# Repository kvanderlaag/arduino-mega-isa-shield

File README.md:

# Arduino Mega 2560 ISA Card Shield
 
 Diagnostic/Development shield for IBM PC XT/AT ISA cards.

 ## God, now what?
 
 Okay, listen. Sometimes you're developing an ISA card, and you fuck it up. Sometimes you want to be able to give that card a set of known inputs for a bus state, and probe around on the card to see why it's not doing what you expect. If we're being honest, that's usually pretty hard when the card is installed in a machine! Arduinos are easy as hell to write simple firmware for, so this is a shield (in an extremely non-standard form factor, you won't be stacking anything on top of this) that breaks most of the useful ISA signals out to an ISA card slot. Pin assignment is set up so that things generally live on sequential port pins wherever possible, and all of the weird ports that you don't get all of the pins for are set up so that they're grouped by whether they're expected to be driven by the bus master, or the card. (i.e. whether you're going to be reading or writing them from the Arduino.) This _should_ allow for reasonably fast access to setting/reading bus state.
 
 ## Does it suck?

Yes, the Arduino Mega 2560 is an 8MHz 8-bit AVR, it's going to be too slow to keep up with 14.31818 MHz ISA signalling in the strictest sense. This isn't going to be useful as a bus emulator, but for basic poking at cards and testing logic, it will work for a lot of cases.

## What sort of features does it have?

It breaks out the full 16-bit data bus, the full address bus for a 16-bit card, and all of the control signals you should need for both 8 and 16-bit reads and writes. Due to the number of available I/O pins on the arduino, it does only provide a small number of DMA channels and interrupts. Specifically, IRQ 2/9, 3, 5, and 7, and DMA channels 1, 3, 5, and 7. I'm using this mostly to test sound cards, for which these are all reasonable options -- it would probably be a good idea to add a jumper block to switch at least one of these out between the remaining options.

The Renesas clock generator/multiplier on the board produces a 14.31818MHz clock signal on the bus clock pin. If your card is using this pin to clock another part (like a Yamaha FM chip, or an SAA1099 sound generator, for instance), this will supply the correct frequency, but the Arduino won't be able to keep up with it. I'm interested to know how well this works for a variety of applications, so if you use this for anything, let me know!

## What AVR ports map to which ISA signals?

Pins not listed in a port are reserved for system use on the Arduino, so maybe don't read from or write to them.

### Port A

| AVR Pin | ISA Signal |
| --- | --- |
| PA0 | D0 |
| PA1 | D1 |
| PA2 | D2 |
| PA3 | D3 |
| PA4 | D4 |
| PA5 | D5 |
| PA6 | D6 |
| PA7 | D7 |

### Port B

| AVR Pin | ISA Signal |
| --- | --- |
| PB0 | A0 |
| PB1 | A1 |
| PB2 | A2 |
| PB3 | A3 |
| PB4 | A4 |
| PB5 | A5 |
| PB6 | A6 |
| PB7 | A7 |

### Port C

| AVR Pin | ISA Signal |
| --- | --- |
| PC0 | SD8 |
| PC1 | SD9 |
| PC2 | SD10 |
| PC3 | SD11 |
| PC4 | SD12 |
| PC5 | SD13 |
| PC6 | SD14 |
| PC7 | SD15 |

### Port D

| AVR Pin | ISA Signal |
| --- | --- |
| PD0 | A16 |
| PD1 | A17 |
| PD2 | A18 |
| PD3 | A19 |
| PD7 | AEN |

### Port E

| AVR Pin | ISA Signal |
| --- | --- |
| PE0 | RESET |
| PE1 | ALE |
| PE2 | SBHE |
| PE3 | ~MEMR |
| PE5 | ~MEMW |

### Port F

| AVR Pin | ISA Signal |
| --- | --- |
| PF0 | A8 |
| PF1 | A9 |
| PF2 | A10 |
| PF3 | A11 |
| PF4 | A12 |
| PF5 | A13 |
| PF6 | A14 |
| PF7 | A15 |

### Port G

| AVR Pin | ISA Signal |
| --- | --- |
| PG0 | ~IOR |
| PG1 | ~IOW |
| PG2 | ~SMEMR |
| PG5 | ~SMEMW |

### Port H

| AVR Pin | ISA Signal |
| --- | --- |
| PH0 | ~DACK1 |
| PH1 | ~DACK3 |
| PH2 | ~DACK5 |
| PH3 | ~DACK7 |
| PH5 | T/C |
| PH6 | ~IO_RDY |

### Port J

| AVR Pin | ISA Signal |
| --- | --- |
| PJ0 | ~NOWS |
| PJ1 | ~IOCS16 |

### Port K

| AVR Pin | ISA Signal |
| --- | --- |
| PK0 | LA17 |
| PK1 | LA18 |
| PK2 | LA19 |
| PK3 | LA20 |
| PK4 | LA21 |
| PK5 | LA22 |
| PK6 | LA23 |
| PK7 | ~MASTER |

### Port L

| AVR Pin | ISA Signal |
| --- | --- |
| PL0 | DRQ1 |
| PL1 | DRQ3 |
| PL2 | DRQ5 |
| PL3 | DRQ7 |
| PL4 | IRQ2 |
| PL5 | IRQ3 |
| PL6 | IRQ5 |
| PL7 | IRQ7 |

## How do I write firmware for it to access an ISA card?

If you're not sure, this project might not be applicable to your use case. In short, take a look at these pages:
https://www.robots.ox.ac.uk/~adutta/blog/interfacing-with-the-isa-bus.html
http://wearcam.org/ece385/lecture6/isa.htm

and then use the Arduino to read/write the appropriate signals to the mapped ports, appropriate to your card's behaviour.

## What do I need to build it?

Part values are all marked on the board, so there should be no confusion about what goes where. Also the only things that have different values and the same footprint are the 27pf and 0.1uF ceramic capacitor, so as long as you don't fuck that up, you should be fine. Just make sure the pin headers point _downward_.

- 1x ISA card slot, EDAC 395-098-520-350 - https://www.digikey.ca/en/products/detail/edac-inc/395-098-520-350/210780
- 1x 3.579545MHz HC-49/US crystal - https://www.digikey.ca/en/products/detail/raltron-electronics/AS-3-579545-18/10246240
- 1x JST-VH 6-pin male header (I would recommend a right angle) - https://www.digikey.ca/en/products/detail/jst-sales-america-inc/B6PS-VH-LF-SN/926559
- 1x Renesas 501MILFT clock generator - https://www.digikey.ca/en/products/detail/renesas-electronics-america-inc/501MILFT/1915335
- 1x 0.1uF ceramic capcitor, through-hole, 2.50mm pitch - https://www.digikey.ca/en/products/detail/vishay-beyschlag-draloric-bc-components/K104K15X7RF5TL2/286538
- 2x 27pF ceramic capcitor, through-hole, 2.50mm pitch - https://www.digikey.ca/en/products/detail/vishay-beyschlag-draloric-bc-components/K270J15C0GF5TL2/286460
- 3x 10uF 16V electrolytic capacitor, through-hole, radial - https://www.digikey.ca/en/products/detail/panasonic-electronic-components/ECA-1CM100I/2688653
- 1x 2.54mm pin header, 2x18 position - https://www.digikey.ca/en/products/detail/w%C3%BCrth-elektronik/61303621121/4846882
- 1x 2.54mm pin header, 1x10 position - https://www.digikey.ca/en/products/detail/adam-tech/PH1-10-UA/9830653
- 5x 2.54mm pin header, 1x8 position - https://www.digikey.ca/en/products/detail/adam-tech/PH1-08-UA/9830442

- 1x PCB - Gerbers in /gerbil/arduino-mega-isa-shield.zip

Total BOM should be about $30 CAD, plus the board.

I've opted to just mount regular pin headers to the bottom of the board since nothing is stacking through, but you could use long-pinned female receptacles instead if you want to be able to shove jumper wires into things for test leads; I'm not your dad, do what you want.

You probably don't need standoffs for the shield itself, but I've provided two 3.5mm holes for the part that overhangs the Arduino with the ISA card slot on it. M3 brass or nylon non-threaded standoffs approximately 12.5mm in length, plus a couple of M3 machine screws, should give it a bit of rigidity if you've just got it sitting flat on a surface. If you're building a mount for the whole contraption, mount it however you'd like.

## Notes on Power

The shield also expects to supply the card with +5V, +12V, and -12V from the JST-VH connector. (The pinout is marked on the board for when you're building a harness.) You'll probably want some sort of small off-board AC/DC converter, some 16-18awg wire, and a harness to connect the two together. You'll also need a way to connect the power supply to mains, which I am _absolutely_ not going to cover here. If you're uncomfortable working with mains wiring, get someone who isn't to do it, or buy an enclosed power supply that already has an inlet and shit. 

I would recommend the following parts, if you're building your own enclosure:

- Power Supply: Meanwell RPT-60B - https://www.digikey.ca/en/products/detail/mean-well-usa-inc/RPT-60B/7706127
- AC harness female connector housing - https://www.digikey.ca/en/products/detail/jst-sales-america-inc/VHR-3N/608625
- DC harness female connector housing - https://www.digikey.ca/en/products/detail/jst-sales-america-inc/VHR-6M/1878656 (get two)
- Contacts - https://www.digikey.ca/en/products/detail/jst-sales-america-inc/SVH-41T-P1-1/608760 (get fifteen - three for the mains harness, twelve for the DC harness. Consider getting more if you're not good at crimping.)
- AC inlet - https://www.amazon.ca/Artrinck-Socket-Rocker-Switch-IEC320/dp/B07DMKBZ9R/ but frankly, your needs will vary depending on whether you want a snap-in or screw-in housing, and I would definitely recommend stuffing a much smaller fuse in there. (If you're drawing 10A off one ISA card, something is seriously wrong.) Either way, get something with a switch so you can kill it if you need to, and for the love of god get one that has a fuse holder if you're using this to test cards that you've designed yourself.

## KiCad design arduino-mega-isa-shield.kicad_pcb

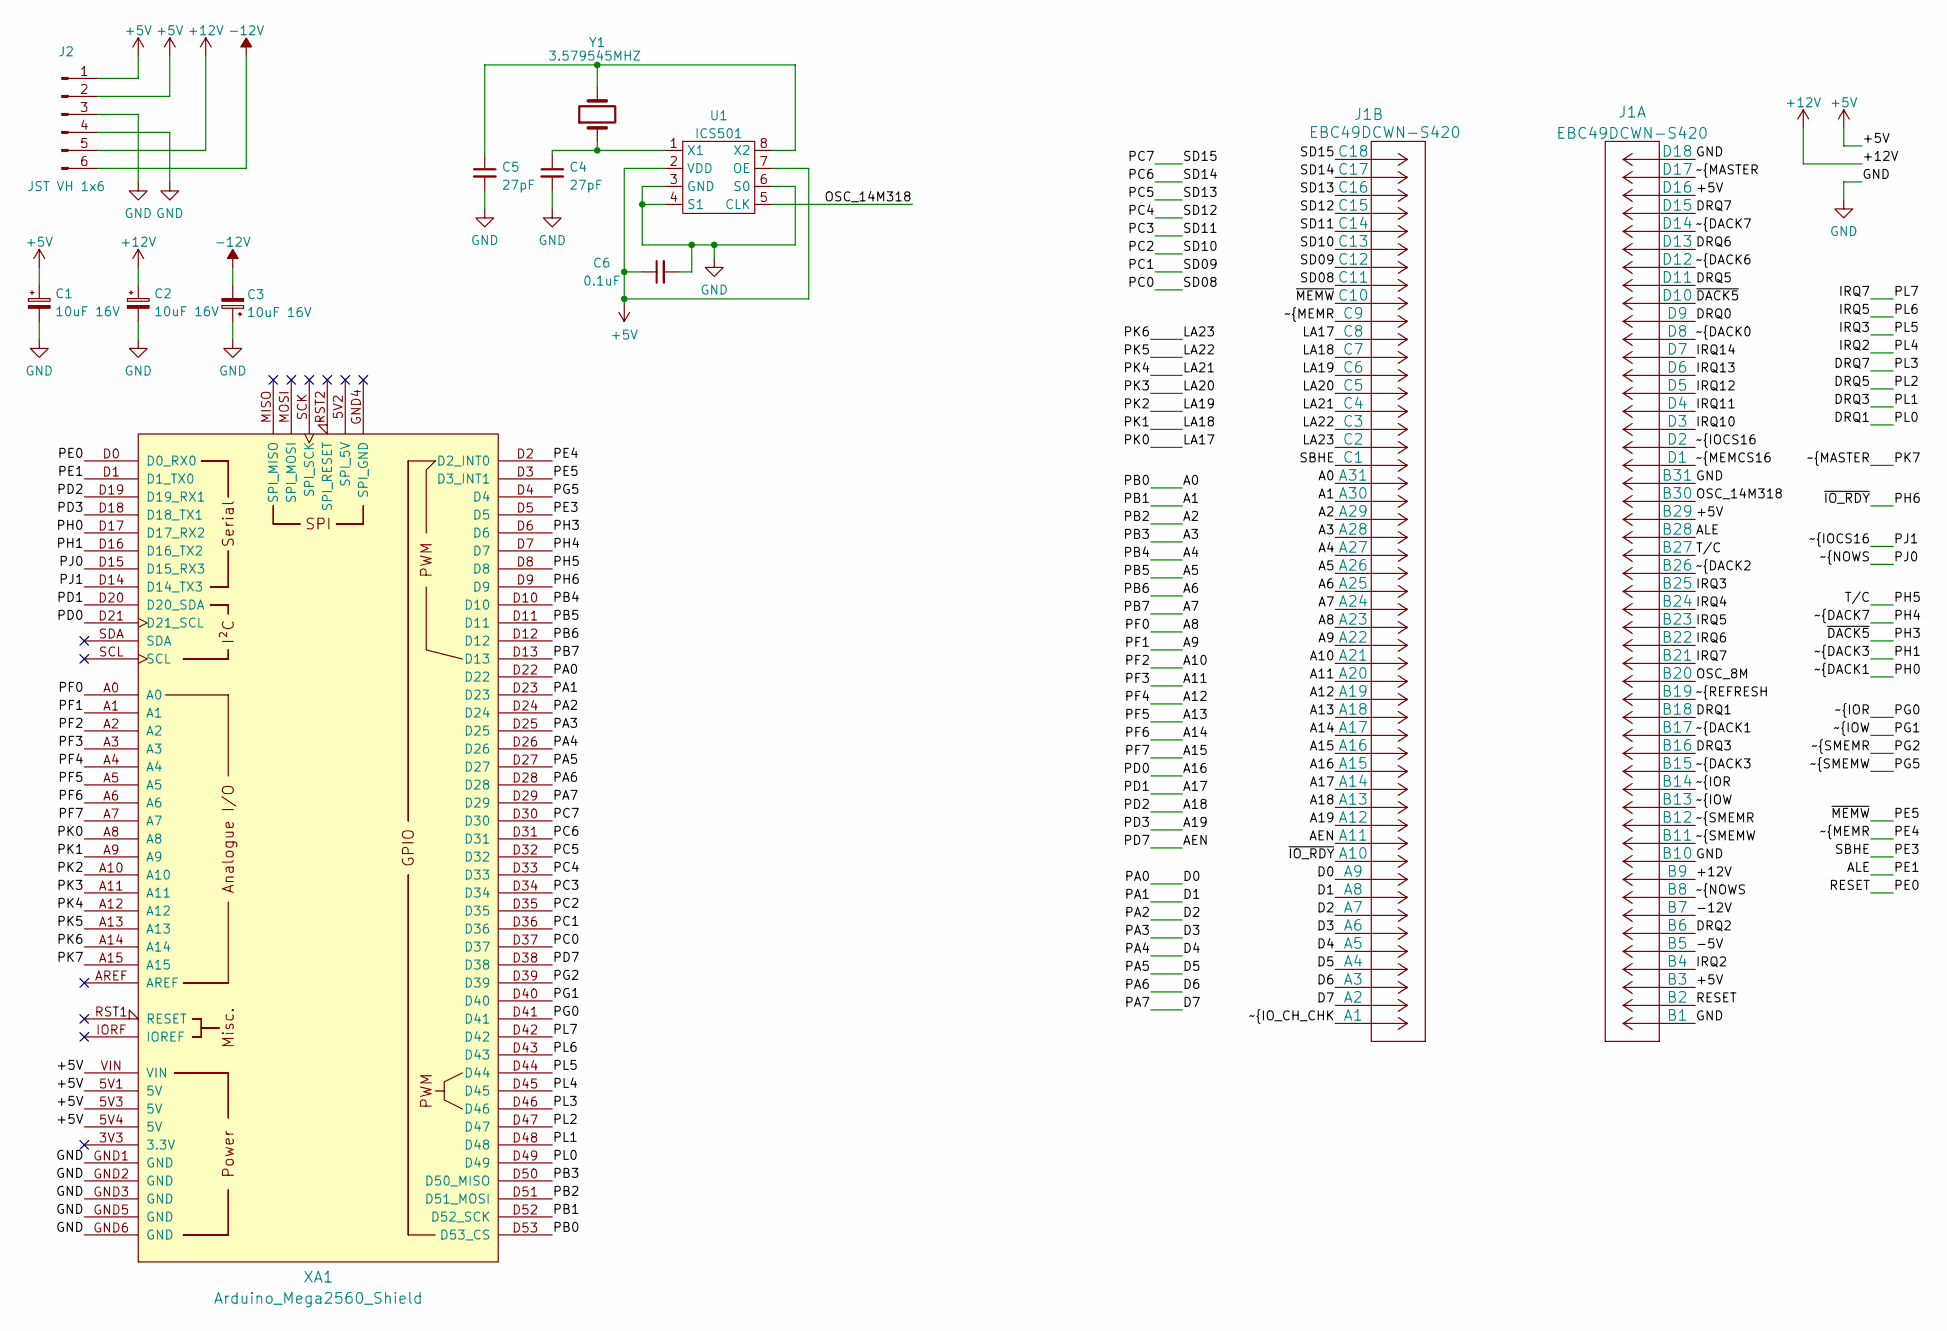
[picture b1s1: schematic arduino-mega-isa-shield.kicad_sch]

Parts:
C1, C2, C3: 10uF 16V; CP_Radial_D6.3mm_P2.50mm
C4, C5: 27pF; C_Disc_D3.8mm_W2.6mm_P2.50mm
C6: 0.1uF; C_Disc_D3.8mm_W2.6mm_P2.50mm
J1: EBC49DCWN-S420
J2: JST VH 1x6; JST_VH_B6PS-VH_1x06_P3.96mm_Horizontal
U1: ICS501; SOIC-8_3.9x4.9mm_P1.27mm
XA1: Arduino_Mega2560_Shield
Y1: 3.579545MHZ; Crystal_HC49-U_Vertical

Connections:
+5V: C1.1, C6.1, J1.3 (D16), J1.21 (B29), J1.47 (B3), J2.1, J2.2, U1.2 (VDD), U1.7 (OE), XA1.5V1 (5V), XA1.5V3 (5V), XA1.5V4 (5V), XA1.VIN
+12V: C2.1, J1.41 (B9), J2.5
-12V: C3.2, J1.43 (B7), J2.6
/-5V: J1.45 (B5)
/A0: J1.68 (A31), XA1.D53 (D53_CS)
/A1: J1.69 (A30), XA1.D52 (D52_SCK)
/A2: J1.70 (A29), XA1.D51 (D51_MOSI)
/A3: J1.71 (A28), XA1.D50 (D50_MISO)
/A4: J1.72 (A27), XA1.D10
/A5: J1.73 (A26), XA1.D11
/A6: J1.74 (A25), XA1.D12
/A7: J1.75 (A24), XA1.D13
/A8: J1.76 (A23), XA1.A0
/A9: J1.77 (A22), XA1.A1
/A10: J1.78 (A21), XA1.A2
/A11: J1.79 (A20), XA1.A3
/A12: J1.80 (A19), XA1.A4
/A13: J1.81 (A18), XA1.A5
/A14: J1.82 (A17), XA1.A6
/A15: J1.83 (A16), XA1.A7
/A16: J1.84 (A15), XA1.D21 (D21_SCL)
/A17: J1.85 (A14), XA1.D20 (D20_SDA)
/A18: J1.86 (A13), XA1.D19 (D19_RX1)
/A19: J1.87 (A12), XA1.D18 (D18_TX1)
/AEN: J1.88 (A11), XA1.D38
/ALE: J1.22 (B28), XA1.D1 (D1_TX0)
/D0: J1.90 (A9), XA1.D22
/D1: J1.91 (A8), XA1.D23
/D2: J1.92 (A7), XA1.D24
/D3: J1.93 (A6), XA1.D25
/D4: J1.94 (A5), XA1.D26
/D5: J1.95 (A4), XA1.D27
/D6: J1.96 (A3), XA1.D28
/D7: J1.97 (A2), XA1.D29
/DRQ0: J1.10 (D9)
/DRQ1: J1.32 (B18), XA1.D49
/DRQ2: J1.44 (B6)
/DRQ3: J1.34 (B16), XA1.D48
/DRQ5: J1.8 (D11), XA1.D47
/DRQ6: J1.6 (D13)
/DRQ7: J1.4 (D15), XA1.D46
/IRQ2: J1.46 (B4), XA1.D45
/IRQ3: J1.25 (B25), XA1.D44
/IRQ4: J1.26 (B24)
/IRQ5: J1.27 (B23), XA1.D43
/IRQ6: J1.28 (B22)
/IRQ7: J1.29 (B21), XA1.D42
/IRQ10: J1.16 (D3)
/IRQ11: J1.15 (D4)
/IRQ12: J1.14 (D5)
/IRQ13: J1.13 (D6)
/IRQ14: J1.12 (D7)
/LA17: J1.60 (C8), XA1.A8
/LA18: J1.61 (C7), XA1.A9
/LA19: J1.62 (C6), XA1.A10
/LA20: J1.63 (C5), XA1.A11
/LA21: J1.64 (C4), XA1.A12
/LA22: J1.65 (C3), XA1.A13
/LA23: J1.66 (C2), XA1.A14
/OSC_8M: J1.30 (B20)
/OSC_14M318: J1.20 (B30), U1.5 (CLK)
/PC0: J1.57 (C11), XA1.D37
/PC1: J1.56 (C12), XA1.D36
/PC2: J1.55 (C13), XA1.D35
/PC3: J1.54 (C14), XA1.D34
/PC4: J1.53 (C15), XA1.D33
/PC5: J1.52 (C16), XA1.D32
/PC6: J1.51 (C17), XA1.D31
/PC7: J1.50 (C18), XA1.D30
/PE0: J1.48 (B2), XA1.D0 (D0_RX0)
/PE3: J1.67 (C1), XA1.D5
/PE4: J1.59 (C9), XA1.D2 (D2_INT0)
/PE5: J1.58 (C10), XA1.D3 (D3_INT1)
/PG0: J1.36 (B14), XA1.D41
/PG1: J1.37 (B13), XA1.D40
/PG2: J1.38 (B12), XA1.D39
/PG5: J1.39 (B11), XA1.D4
/PH0: J1.33 (B17), XA1.D17 (D17_RX2)
/PH1: J1.35 (B15), XA1.D16 (D16_TX2)
/PH3: J1.9 (D10), XA1.D6
/PH4: J1.5 (D14), XA1.D7
/PH5: J1.23 (B27), XA1.D8
/PH6: J1.89 (A10), XA1.D9
/PJ0: J1.42 (B8), XA1.D15 (D15_RX3)
/PJ1: J1.17 (D2), XA1.D14 (D14_TX3)
/PK7: J1.2 (D17), XA1.A15
/~DACK0: J1.11 (D8)
/~DACK2: J1.24 (B26)
/~DACK6: J1.7 (D12)
/~IO_CH_CHK: J1.98 (A1)
/~MEMCS16: J1.18 (D1)
/~REFRESH: J1.31 (B19)
GND: C1.2, C2.2, C3.1, C4.2, C5.2, C6.2, J1.1 (D18), J1.19 (B31), J1.40 (B10), J1.49 (B1), J2.3, J2.4, U1.3 (GND), U1.4 (S1), U1.6 (S0), XA1.GND1 (GND), XA1.GND2 (GND), XA1.GND3 (GND), XA1.GND5 (GND), XA1.GND6 (GND)
unnamed: C4.1, U1.1 (X1), Y1.1
unnamed: C5.1, U1.8 (X2), Y1.2

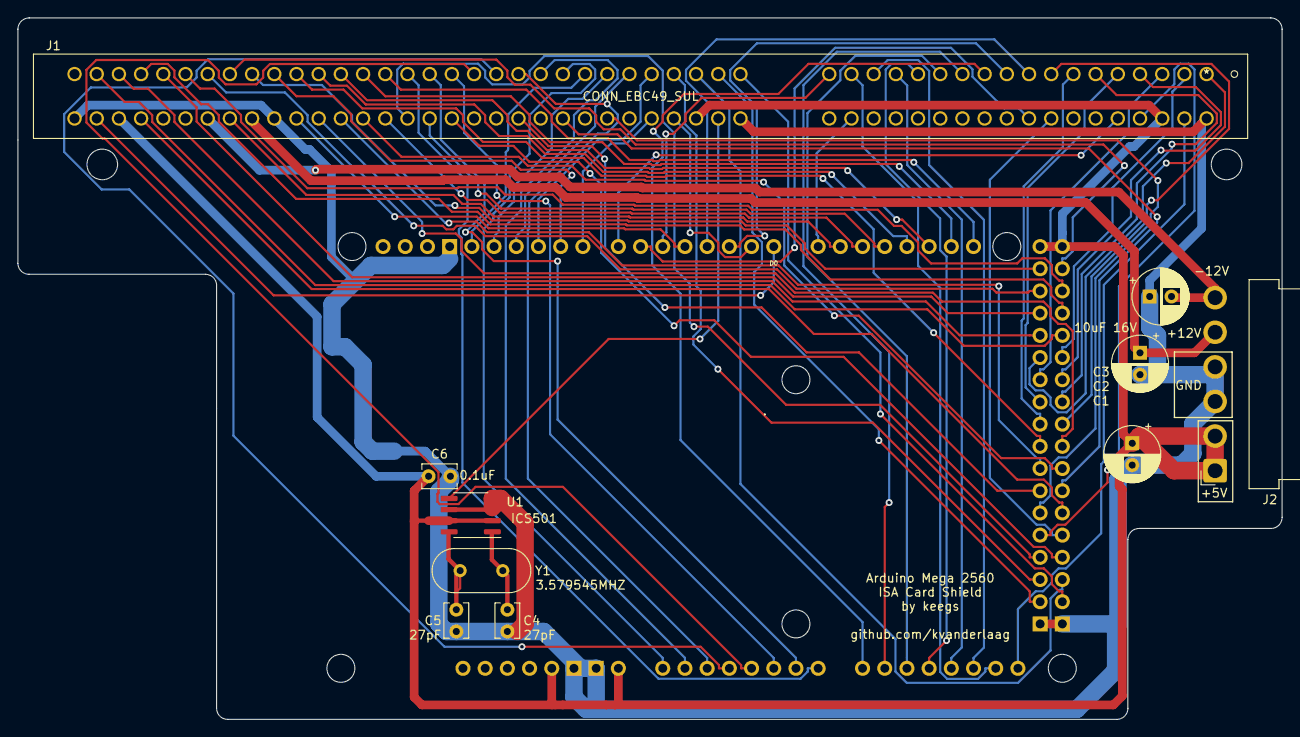
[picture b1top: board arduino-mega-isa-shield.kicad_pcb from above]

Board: 2 copper layers, 144.7 x 80.3 mm, 11 parts (0 on the bottom side), 77 nets.

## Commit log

2023-03-09 Initial project commit
2023-03-11 Update board
2023-03-11 Reverse LA17-LA23 for sequential port access, re-route board
2023-03-11 Update gerbers
2023-03-12 pick a less expensive ISA card connector
2023-03-12 Update board for EDAC 395-098-520-350 ISA connector
2023-03-12 Add DigiKey Bill of Materials CSV
2023-03-12 add 3d models for vanity
2023-03-12 add images to readme
2023-03-28 Move power connector back so it doesn't hang off the board
2023-04-03 Rework board
    lmao the ISA connector pinout was flipped

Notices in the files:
parts and their libraries:
Copyright 2021 Accelerated Designs. All rights reserved.
